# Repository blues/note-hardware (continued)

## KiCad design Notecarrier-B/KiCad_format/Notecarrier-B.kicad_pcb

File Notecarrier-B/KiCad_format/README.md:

# Notecarrier-B

This folder contains the design files for the Blues Wireless Notcarrier-B, in KiCad 7 format. They were generated by porting the original OrCad design files. For a detailed description of the porting process, see [PortingNotes](PortingNotes.md).

Components in this design are sourced from the [blues-kicad-lib](https://github.com/blues/blues-kicad-lib) library. However, with the exception of 3D models, KiCad produces self-contained project files. Thus this project can still be used without access to the library.

## Contents

- This file
 	- `README.md`
- KiCad source files
	- `Notecarrier-B.kicad_pcb`	- `Notecarrier-B.kicad_prl`	- `Notecarrier-B.kicad_pro`	- `Notecarrier-B.kicad_sch`	- `Notecarrier-B.kicad_wks`
	- `sym-lib-table`
	- `fp-info-cache`	- `fp-lib-table`
- Documentation	- `documentation/*`
- Manufacturing artefacts
	- `manufacturing/*`
- Design references
	- `reference/*`
- Validation artefacts
	- `validation/*`

## Revision History

| Revision |    Date    |   Author   | Description |
|:--------:| ---------- | ---------- | ----------- |
|     A    | 2023-03-31 | H.Raftery  | initial port from OrCAD design files, rev 14 (v2.1). |

### Original OrCad Design File Revision History

| Revision |    Date    |   Author   | Description |
|:--------:| ---------- | ---------- | ----------- |
|    12    | 25/08/2020 | G.Boschini | - Changed screw with inox version<br/>- Changed pullup resistor of EN pin to 10M |
|    14    | 25/08/2020 | M. Gregis  | - Added LiPO charger<br/>- Changed V+ to VBAT<br/>- removed BOOT signal from J21 header and replaced with GND<br/>- removed AUX5 from J22 header and replaced with VMODEM |

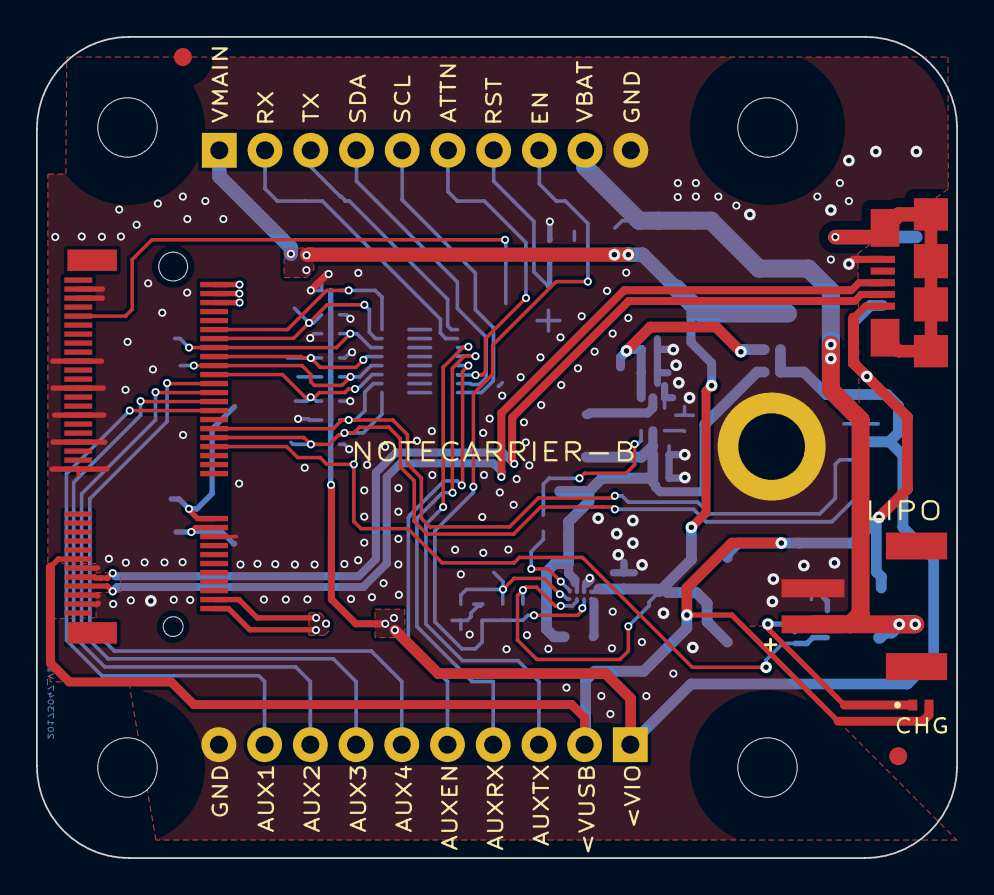
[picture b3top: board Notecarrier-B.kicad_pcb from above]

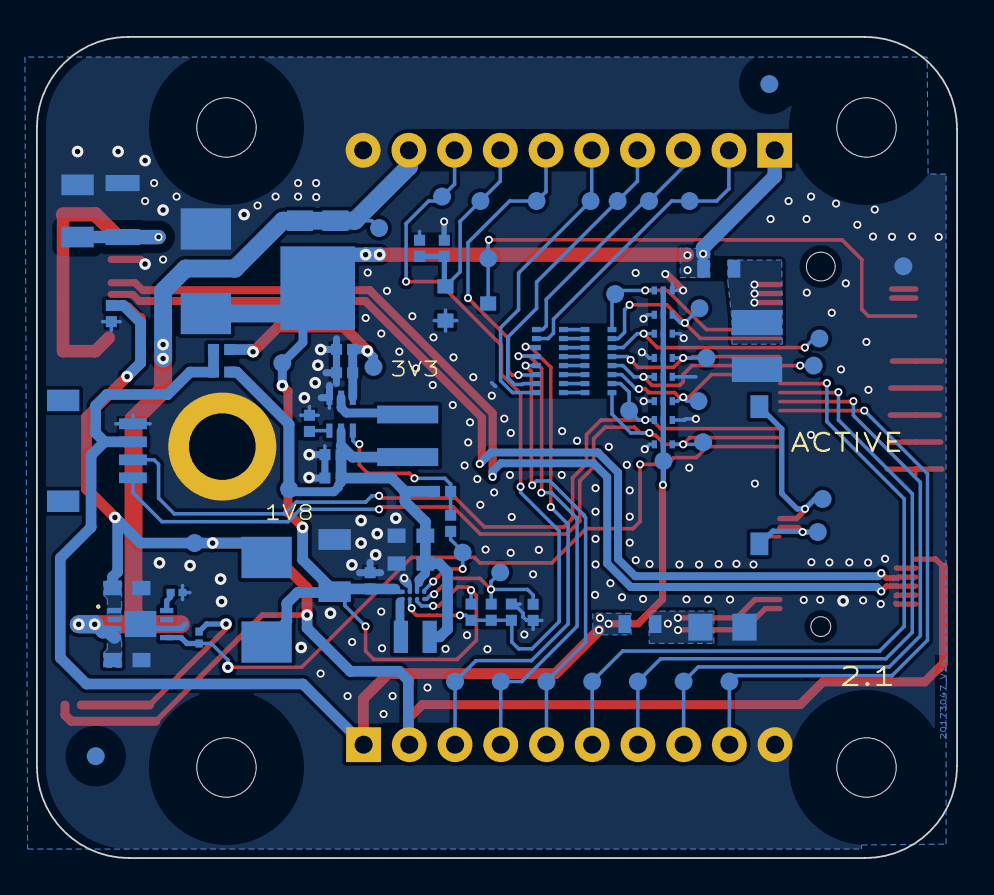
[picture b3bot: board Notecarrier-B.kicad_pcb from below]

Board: 2 copper layers, 51.1 x 45.6 mm, 96 parts (85 on the bottom side), 54 nets.

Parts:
C7, C10, C111, C115, C116: 100n/16V; CS-C-0402_NO-FILL
C8, C9: 10u/6.3V-X5R; CS-C-0402_NO-FILL
C13: 47u/16V-X5R; CS-C-1206
C14: 4.7u/6.3V-X5R; CS-C-0402_NO-FILL
C15, C16: 10u/10V-X5R; CS-C-0603
C112: 10n/1kV; CS-C-1206
C113: NU; CS-T-A
C114: NU; CS-T-B
C117, C118: 4.7u/10V/X5R; CS-C-0603
DS4, DS5, DS6, DS10: NU; SOT563
DS14: STPS3H100U; SMB
DS15: FSV1045V; TO277-3
DSW1: DIP-SW-CHS-01TB; DSS-CHS-01TB
F1: SF-0603F150-2; FS-0603
F2: 3.5A/32V; FS-0603
FID1, FID2, FID3, FID4: TPS; FIDUCIAL
H1, H2, H3, H4: MountingHole; FORO-0330-U
J19: MICROUSB-B; J-5-0065-FOS-MICROUSB10118192
J20: MDT420E01001; J-75-0050-MOS-M2-E
J21, J22: NU; J-10-0254-MDT
J23: S2B-PH-SM4-TB(LF)(SN); J-2-0200-MOS-S2B
J24: SM04B-SRSS-TBT; J-4-0100-MOS-SH
L2: 1285AS-H-2R2M=P2; LS-0806
L4: XFL4020-222MEC; LS-XFL4020
LD1: SML-P12WTT86R; LD-0402
OBJ1: 9774025151R; DIST-WASMSIM0250
Q2: AO3420; SOT23_NO-FILL
R5: 1k; RS-0201_NO-FILL
R6: 82k; RS-0402_NO-FILL
R7: 2.8k; RS-0201_NO-FILL
R10: 10M/5%; RS-0402_NO-FILL
R307: 1M; RS-1206
R318, R322, R325: 0R; RS-0402_NO-FILL
R319: 1k; RS-0402_NO-FILL
R323, R324, R326: NU; RS-0402_NO-FILL
RR1, RR2: 100R/5%; RR-8X-1506
TP1, TP2, TP3, TP4, TP5, TP6, TP7, TP8, TP10, TP11, TP12, TP13, TP14, TP15, TP17, TP18, TP20, TP21, TP22, TP23, TP24, TP25, TP26, TP28, TP29, TP30, TP31, TP32, TP33, TP34, TP38, TP39: TPS-SPEA
TVS1: SM6T6V8A; SMB
U3: MAX17225ELT; WDFN6-0200X0200
U4: TPS62748YFPT; XFBGA8
U5: MCP73831-2ACI/MC; VFDFN8-EXP
VMODEM: TPS-SPEA
VUSB: TPS-SPEA

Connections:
+1V8: C9.1, C10.1, C15.1, C16.1, L2.2, L4.2, R318.2, R326.2, TP12.1, U3.5 (IN), U4.C2 (VOS)
+3V3: C7.1, C8.1, R325.2, TP20.1, U3.1 (OUT)
/ATTN: J22.6, RR1.6 (R6.1), TP32.1
/ATTN_P: DS6.6 (K1A2), J20.54 (ATTN_P), RR2.11 (R6.2), TP18.1
/AUX1: J20.46 (AUX1), J21.9, TP1.1
/AUX2: J20.48 (AUX2), J21.8, TP2.1
/AUX3: J20.50 (AUX3), J21.7, TP3.1
/AUX4: J20.52 (AUX4), J21.6, TP7.1
/AUX5: J20.38 (NC38), R5.1, U5.5 (STAT)
/AUX_EN: J21.5, RR1.5 (R5.1), TP4.1
/AUX_EN_P: DS6.3 (K3A4), J20.56 (AUX_EN_P), RR2.12 (R5.2), TP21.1
/AUX_RX: J21.4, RR1.4 (R4.1), TP5.1
/AUX_RX_P: DS5.6 (K1A2), J20.58 (AUX_RX_P), RR2.13 (R4.2), TP22.1
/AUX_TX: J21.3, RR1.3 (R3.1), TP6.1
/AUX_TX_P: DS5.3 (K3A4), J20.60 (AUX_TX_P), RR2.14 (R3.2), TP23.1
/BOOST_EN: R324.2, TP10.1, U4.D2 (LOAD)
/EN: C116.1, J22.8, R10.1, R323.2, TP34.1, U4.B1 (EN)
/NRST: J20.67 (NRST), Q2.3 (D), TP26.1
/RST: C115.1, J22.7, Q2.1 (G), R319.2, TP33.1
/RX: J22.2, RR1.2 (R2.1), TP28.1
/RX_P: DS10.6 (K1A2), J20.62 (RX_P), RR2.15 (R2.2), TP24.1
/SCL: J22.5, RR1.8 (R8.1), TP31.1
/SCL_P: DS4.6 (K1A2), J20.40 (SCL_P), J24.4, RR2.9 (R8.2), TP15.1
/SDA: J22.4, RR1.7 (R7.1), TP30.1
/SDA_P: DS4.3 (K3A4), J20.42 (SDA_P), J24.3, RR2.10 (R7.2), TP17.1
/TX: J22.3, RR1.1 (R1.1), TP29.1
/TX_P: DS10.3 (K3A4), J20.64 (TX_P), RR2.16 (R1.2), TP25.1
/USB_DM: J19.2 (D-), J20.9 (USB_DM)
/USB_DP: J19.3 (D+), J20.7 (USB_DP)
GND: C7.2, C8.2, C9.2, C10.2, C13.2, C14.2, C15.2, C16.2, C111.2, C112.2, C113.2, C114.2, C115.2, C116.2, C117.2, C118.2, DS4.1 (A1), DS4.4 (A3), DS5.1 (A1), DS5.4 (A3), DS6.1 (A1), DS6.4 (A3), DS10.1 (A1), DS10.4 (A3), J19.5 (GND), J20.3 (GND), J20.5 (GND), J20.6 (GND), J20.11 (GND), J20.18 (GND), J20.33 (GND), J20.39 (GND), J20.45 (GND), J20.51 (GND), J20.57 (GND), J20.71 (GND), J20.73 (GND), J21.10, J22.10, J23.2, J24.1, OBJ1.1, Q2.2 (S), R6.1, R7.1, R307.2, R319.1, R322.1, TP38.1, TVS1.2 (A2), U3.3 (GND), U4.B2 (GND), U5.6 (V_{SS}), U5.9 (EP)
unnamed: C112.1, J19.6 (Shield), R307.1
unnamed: DSW1.1, J20.22 (VACT_GPS_IN)
unnamed: LD1.1 (K), R5.2
unnamed: RR1.16 (R1.2), RR2.1 (R1.1)
unnamed: RR1.15 (R2.2), RR2.2 (R2.1)
unnamed: RR1.14 (R3.2), RR2.3 (R3.1)
unnamed: RR1.13 (R4.2), RR2.4 (R4.1)
unnamed: RR1.12 (R5.2), RR2.5 (R5.1)
unnamed: RR1.11 (R6.2), RR2.6 (R6.1)
unnamed: RR1.10 (R7.2), RR2.7 (R7.1)
unnamed: RR1.9 (R8.2), RR2.8 (R8.1)
unnamed: R318.1, R324.1, U3.6 (EN)
unnamed: L4.1, U3.2 (LX)
unnamed: R6.2, U3.4 (SEL)
unnamed: R322.2, R323.1, TP8.1, U4.D1 (CTRL)
unnamed: L2.1, U4.A1 (SW)
unnamed: R7.2, U5.8 (PROG)
VACT_GPS_OUT: DSW1.2, J20.20 (VACT_GPS_OUT), TP11.1
VBAT: C117.1, DS15.1 (A1), DS15.2 (A2), J22.9, J23.1, TP39.1, U5.3 (V_{BAT}), U5.4 (V_{BAT})
VIO: DS4.2 (K2), DS4.5 (K4), DS5.2 (K2), DS5.5 (K4), DS6.2 (K2), DS6.5 (K4), DS10.2 (K2), DS10.5 (K4), F1.1, J21.1, J24.2, R325.1, R326.1, TP14.1
VIO_P: C113.1, F1.2, J20.2 (VIO_P), J20.4 (VIO_P)
VMODEM: C13.1, C14.1, DS14.1 (K), DS15.3 (C), F2.1, J22.1, R10.2, TVS1.1 (A1), U4.A2 (VIN), U4.C1 (VSEL), VMODEM.1
VMODEM_P: C114.1, F2.2, J20.70 (VMODEM_P), J20.72 (VMODEM_P), J20.74 (VMODEM_P)
VUSB: C111.1, C118.1, DS14.2 (A), J19.1 (VBUS), J20.13 (VUSB), J21.2, LD1.2 (A), U5.1 (V_{DD}), U5.2 (V_{DD}), VUSB.1

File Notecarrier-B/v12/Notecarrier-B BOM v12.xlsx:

PROJECT |  | 2017-3047 (NOTECARRIER-M2-B) |  | Blues Inc
REVISION |  | 12
SCHEMATIC |  | 20173047_NOTECARRIER-M2-B_V12
DATA |  | 25/08/2020
Item | Quantity | Reference | Part | MPN | Description | Temperature | Type | Package
1 | 1 | CS1 | CS V11 2L 35um |  | C.S. NOTECARRIER-M2-B V11 (45.62X45.62)mm 2L/SO/SR ENIG TG150 sp=1.6mm Cu=35um | TG150
2 | 5 | C7,C10,C111,C115,C116 | 100n/16V |  | CHIP CERAMIC CAPACITOR 100nF 16V 10% X7R 0402 |  | SMD | CS-C-0402
3 | 2 | C8,C9 | 10u/6.3V-X5R |  | CHIP CERAMIC CAPACITOR 10uF 6.3V 20% X5R 0402 | -55°..+85° | SMD | CS-C-0402
4 | 1 | C13 | 47u/16V-X5R |  | CHIP CERAMIC CAPACITOR 47uF 16V 20% X5R 1206 |  | SMD | CS-C-1206
5 | 1 | C14 | 4.7u/6.3V-X5R |  | CHIP CERAMIC CAPACITOR 4.7uF 6.3V 20% X5R 0402 |  | SMD | CS-C-0402
6 | 2 | C15,C16 | 10u/10V-X5R |  | CHIP CERAMIC CAPACITOR 10uF 10V 10% X5R 0603 |  | SMD | CS-C-0603
7 | 1 | C112 | 10n/1kV |  | CHIP CERAMIC CAPACITOR 10nF 1000V 10% X7R 1206 |  | SMD | CS-C-1206
8 | 1 | DS14 | STPS3H100U | STPS3H100U | DIODE SCHOTTKY 3A 100V STPS3H100U SMB SMT |  | SMD | SMB
9 | 1 | DS15 | FSV1045V | FSV1045V | DIODE SCHOTTKY 10A 45V FSV1045V TO277-3 SMT | -55°..+150° | SMD | TO277-3
10 | 1 | F1 | SF-0603F150-2 | SF-0603F150-2 | FAST BLOW FUSE 1.5A 32V 0603 SF-0603F150-2 BOURNS SMT | -40°..+105° | SMD | FS-0603
11 | 1 | F2 | 3.5A/32V | 0603SFV350F/32-2 | FAST BLOW FUSE 3.5A 32V 0603 0603SFV350F/32-2 LITTELFUSE SMT | -55°..+125° | SMD | FS-0603
12 | 1 | J19 | MICROUSB-B | 10118192-0001LF | CONNECTOR USB F/90° TIPO MICRO-B C.S. 10118192-0001LF FCI SMT | -30°..+85° | SMD | J-5-0065-FOS-MICROUSB10118192
13 | 1 | J20 | MDT420E01001 |  | CONNECTOR M.2 75P M/90° P=0.5 MDT420E01001 AMPHENOL SMT | -40°..+80° | SMD | J-75-0050-MOS-M2-E
14 | 1 | J21 | HEADER STRIP 9 PIN |  | HEADER STRIP 1P M/D P=2.54 CH3140V100 |  | THT | J-10-0254-MDT
15 | 1 | J22 | HEADER STRIP 9 PIN |  | HEADER STRIP 1P M/D P=2.54 CH3140V100 |  | THT | J-9-0254-MDT
16 | 1 | L2 | 1285AS-H-2R2M=P2 | 1285AS-H-2R2M=P2 | INDUCTOR 2.2uH 1.5A 20% 0806 1285AS-H-2R2M=P2 MURATA SMT | -40°..+85° | SMD | LS-0806
17 | 1 | L4 | XFL4020-222MEC | XFL4020-222MEC | INDUCTOR 2.2 uH 3.1A 20% XFL4020-222MEC COILCRAFT SMT | -40°..+125° | SMD | LS-XFL4020
18 | 1 | OBJ1 | 9774025151R |  | ROUND STANDOFF STEEL 5.1X2.5 9774025151R W.E SMT |  | SMD | DIST-WASMSIM0250
19 | 1 | Q2 | AO3420 |  | TRANSISTOR MOSFET N AO3420 SOT-23 ALPHA-OMEGA SMT | -55°..+150° | SMD | SOT23
20 | 2 | RR1,RR2 | 100R/5% |  | RESISTOR NETWORK 8R sing. 100R 5% 1506 CAY16-101J8LF BOURNS SMT | -55°..+125° | SMD | RR-8X-1506
21 | 1 | R6 | 82k |  | CHIP RESISTOR 82K 0402 1/16W 1% | -55°..+155° | SMD | RS-0402
22 | 1 | R10 | 10M/5% |  | CHIP RESISTOR 10M 0402 1/8W 5% | -55°..+125° | SMD | RS-0402
23 | 1 | R307 | 1M |  | CHIP RESISTOR 1M 1206 1/4W 1% |  | SMD | RS-1206
24 | 1 | R317 | 0R/5%/AS |  | CHIP RESISTOR 0R 0805 1/8W 5% ANTI-SULFUR | -55°..+155° | SMD | RS-0805
25 | 2 | R318,R322 | 0R |  | CHIP RESISTOR 0R 0402 1/16W 1% |  | SMD | RS-0402
26 | 1 | R319 | 1k |  | CHIP RESISTOR 1K 0402 1/16W 1% | -55°..+155° | SMD | RS-0402
27 | 1 | SW1 | CJS-1200TA |  | SWITCH SLIDE SPDT ON-ON. CJS-1200TA NIDEC COPAL ELECTRONICS SMT | -40°..+85° | SMD | SW-CJS1200TA
28 | 1 | TVS1 | SM6T6V8A |  | DIODE TVS TRANSIL UNIDIR. 600W 6.8V SM6T6V8A SMB SMT |  | SMD | SMB
29 | 1 | U3 | MAX17225ELT | MAX17225ELT+T | IC MAX17225ELT+T MAXIM W-DFN6 SMT | -40°..+85° | SMD | WDFN6-0200X0200
30 | 1 | U4 | TPS62748YFPT | TPS62748YFPT | IC TPS62748YFPT TEXAS DSBGA8 SMT | -40°..+85° | SMD | XFBGA8
 | 38
MECHANICAL
1 | 1 | ASS1 | SCREW M2.5x4 |  | DIN 912 M2.5x4 HEX SOCKET HEAD CAP SCREW, FULLY-THREADED SHAFT, A2 STAINLESS |  | THT
 | 1
NOT MOUNTED
1 | 1 | C113 | NU | F930J107KAA | CHIP CAP.TANT. 100uF 6.3V 10% CASE A F930J107KAA AVX | -55°..+125° | SMD | CS-T-A
2 | 1 | C114 | NU | F930J227KBA | CHIP CAP.TANT. 220uF 6.3V 10% CASE B F930J227KBA AVX | -55°..+125° | SMD | CS-T-B
3 | 4 | DS4,DS5,DS6,DS10 | NU | BAV99BRVA-7 | DIODE ARRAY 0.2A 75V BAV99BRVA-7 SOT563 DIODES SMT | -65°..+150° | SMD | SOT563
4 | 4 | FID1,FID2,FID3,FID4 | TPS |  | FIDUCIAL |  | SMD | FIDUCIAL
5 | 2 | R323,R324 | NU |  | CHIP RESISTOR 0402 |  | SMD | RS-0402

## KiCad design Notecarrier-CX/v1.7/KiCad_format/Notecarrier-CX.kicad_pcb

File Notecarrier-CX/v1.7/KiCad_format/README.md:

# Notecarrier-CX v1.7 — KiCad format

This directory contains the design files for the Blues **Notecarrier-CX**
v1.7 in **KiCad 9** format. They were generated by porting the original
Altium Designer design files (project `100544_notecarrier-cx`) and validated
against the shipped BOM, the production gerbers, and the shipped ODB++
netlist — see
[`documentation/Porting-Notes.md`](documentation/Porting-Notes.md) and
[`validation/`](validation/).

## Contents

| Path | Description |
|---|---|
| `Notecarrier-CX.kicad_pro` / `Notecarrier-CX.kicad_prl` | KiCad project |
| `Notecarrier-CX.kicad_sch` | Root schematic |
| `Notecarrier-CX_IO-Connection.kicad_sch`, `Notecarrier-CX_Notecard-Connection.kicad_sch`, `Notecarrier-CX_Power.kicad_sch`, `Notecarrier-CX_MCU.kicad_sch` | Child sheets (the Altium cover and block-diagram sheets are not ported) |
| `Notecarrier-CX.kicad_pcb` | 4-layer board (castellated edges; zone fills preserved from the Altium import — do not refill) |
| `Notecarrier-CX.kicad_wks` | Drawing sheet (shared Blues template) |
| `Notecarrier-CX-altium-import.kicad_sym` / `Notecarrier-CX-altium-import.pretty/` | Project symbol/footprint libraries captured during the import |
| `sym-lib-table` / `fp-lib-table` | Library tables (the original Altium lib nicknames are aliased to the project library) |
| `documentation/` | Porting notes and plotted schematic/board PDFs |
| `manufacturing/Notecarrier-CX_RevA.zip` | Gerbers + Excellon drills exported from KiCad (authoritative production package: [`../FAB/`](../FAB/) ) |
| `validation/` | ERC/DRC reports, per-layer gerber diffs, BOM comparison, ODB++ netlist cross-check, KiCanvas screenshots |

The project is self-contained. Note: R4 (0R) is not populated in the
production build and is flagged DNP; the castellated header positions
P1/P2/P4 are bare-board features and are excluded from the BOM, matching
the shipped production BOM.

## Revision History

| Revision | Date | Author | Notes |
|---|---|---|---|
| A | 2026-07-28 | Blues Inc | Initial port of Notecarrier-CX v1.7 from Altium Designer sources, KiCad 9.0.9 |

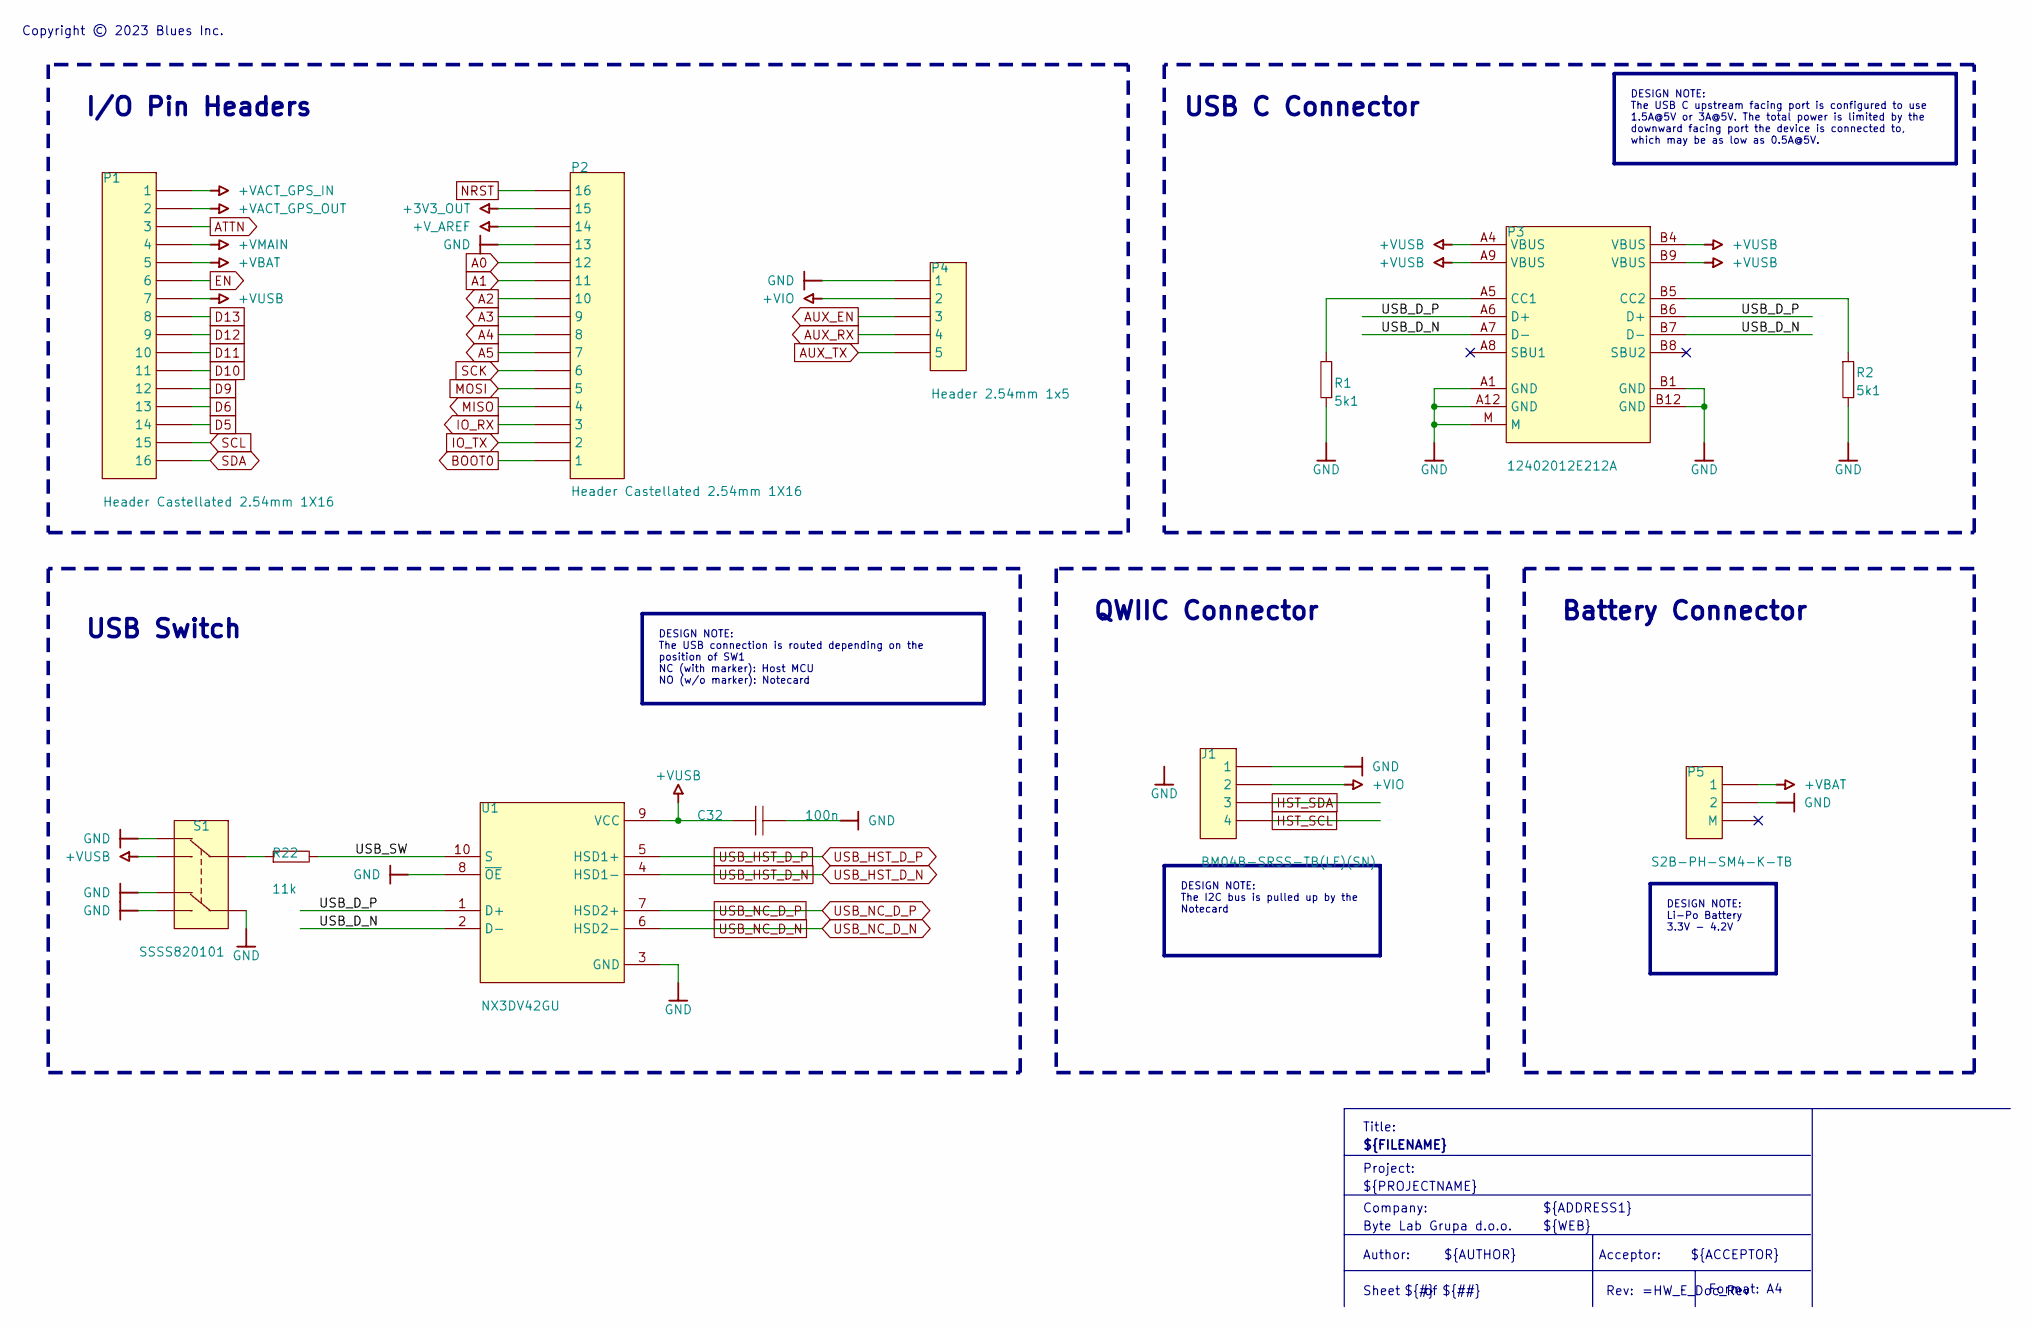
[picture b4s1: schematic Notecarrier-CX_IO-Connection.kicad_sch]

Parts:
C32: 100n; C-0402; MANUFACTURER PART NUMBER N/A
J1: BM04B-SRSS-TB(LF)(SN); Conn BM04B-SRSS-TB(LF)(SN); MANUFACTURER PART NUMBER BM04B-SRSS-TB(LF)(SN)
P1, P2: Header Castellated 2.54mm 1X16; Castellated Header 2.54mm 1X16; MANUFACTURER PART NUMBER N/A
P3: 12402012E212A; CONN_12402012E212A; MANUFACTURER PART NUMBER 12402012E212A
P4: Header 2.54mm 1x5; Castellated Header 2.54mm 1X5; MANUFACTURER PART NUMBER DS1021-1*5SF1-1
P5: S2B-PH-SM4-K-TB; Conn S2B-PH-SM4; MANUFACTURER PART NUMBER S2B-PH-SM4-K-TB(LF)(SN)
R1, R2: 5k1; R-0402; MANUFACTURER PART NUMBER N/A
R22: 11k; R-0402; MANUFACTURER PART NUMBER N/A
S1: SSSS820101; Slide Switch SSSS820101; MANUFACTURER PART NUMBER SSSS820101
U1: NX3DV42GU; QFN40P140X180X50-10N; MANUFACTURER PART NUMBER NX3DV42GU

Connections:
+3V3_OUT: P2.15; also elsewhere on the board
+VACT_GPS_IN: P1.1; also elsewhere on the board
+VACT_GPS_OUT: P1.2; also elsewhere on the board
+VBAT: P1.5, P5.1; also elsewhere on the board
+VIO: J1.2, P4.2; also elsewhere on the board
+VMAIN: P1.4; also elsewhere on the board
+VUSB: C32.2, P1.7, P3.A4 (VBUS), P3.A9 (VBUS), P3.B4 (VBUS), P3.B9 (VBUS), S1.1, U1.9 (VCC); also elsewhere on the board
+V_AREF: P2.14; also elsewhere on the board
/IO Connection/USB_D_N: P3.A7 (D-), P3.B7 (D-), U1.2 (D-)
/IO Connection/USB_D_P: P3.A6 (D+), P3.B6 (D+), U1.1 (D+)
/IO Connection/USB_SW: R22.2, U1.10 (S)
A0: P2.12; also elsewhere on the board
A1: P2.11; also elsewhere on the board
A2: P2.10; also elsewhere on the board
A3: P2.9; also elsewhere on the board
A4: P2.8; also elsewhere on the board
A5: P2.7; also elsewhere on the board
ATTN: P1.3; also elsewhere on the board
AUX_EN: P4.3; also elsewhere on the board
AUX_RX: P4.4; also elsewhere on the board
AUX_TX: P4.5; also elsewhere on the board
BOOT0: P2.1; also elsewhere on the board
D5: P1.14; also elsewhere on the board
D6: P1.13; also elsewhere on the board
D9: P1.12; also elsewhere on the board
D10: P1.11; also elsewhere on the board
D11: P1.10; also elsewhere on the board
D12: P1.9; also elsewhere on the board
D13: P1.8; also elsewhere on the board
EN: P1.6; also elsewhere on the board
GND: C32.1, J1.1, J1.M, P2.13, P3.A1 (GND), P3.A12 (GND), P3.B1 (GND), P3.B12 (GND), P3.M, P4.1, P5.2, R1.1, R2.2, S1.3, S1.4, S1.5, S1.6, U1.3 (GND), U1.8 (~OE); also elsewhere on the board
HST_SCL: J1.4, P1.15; also elsewhere on the board
HST_SDA: J1.3, P1.16; also elsewhere on the board
IO_RX: P2.3; also elsewhere on the board
IO_TX: P2.2; also elsewhere on the board
MISO: P2.4; also elsewhere on the board
MOSI: P2.5; also elsewhere on the board
NRST: P2.16; also elsewhere on the board
unnamed: P3.A5 (CC1), R1.2
unnamed: P3.B5 (CC2), R2.1
unnamed: R22.1, S1.2
SCK: P2.6; also elsewhere on the board
USB_HST_D_N: U1.4 (HSD1-); also elsewhere on the board
USB_HST_D_P: U1.5 (HSD1+); also elsewhere on the board
USB_NC_D_N: U1.6 (HSD2-); also elsewhere on the board
USB_NC_D_P: U1.7 (HSD2+); also elsewhere on the board

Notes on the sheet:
Copyright © 2023 Blues Inc.
${REVISION}
Sheet
${#}
${COMPANY}
Company:
${AUTHOR}
Battery Connector
${FILENAME}
${ACCEPTOR}
Acceptor:
Title:
Author:
${ADDRESS1}
Project:
Rev:
${WEB}
USB C Connector
QWIIC Connector
${PROJECTNAME}
I/O Pin Headers
Format: A4
USB Switch
${##}
DESIGN NOTE: The I2C bus is pulled up by the Notecard
DESIGN NOTE: Li-Po Battery 3.3V - 4.2V
DESIGN NOTE: The USB C upstream facing port is configured to use 1.5A@5V or 3A@5V. The total power is limited by the downward facing port the device is connected to, which may be as low as 0.5A@5V.
DESIGN NOTE: The USB connection is routed depending on the position of SW1 NC (with marker): Host MCU NO (w/o marker): Notecard

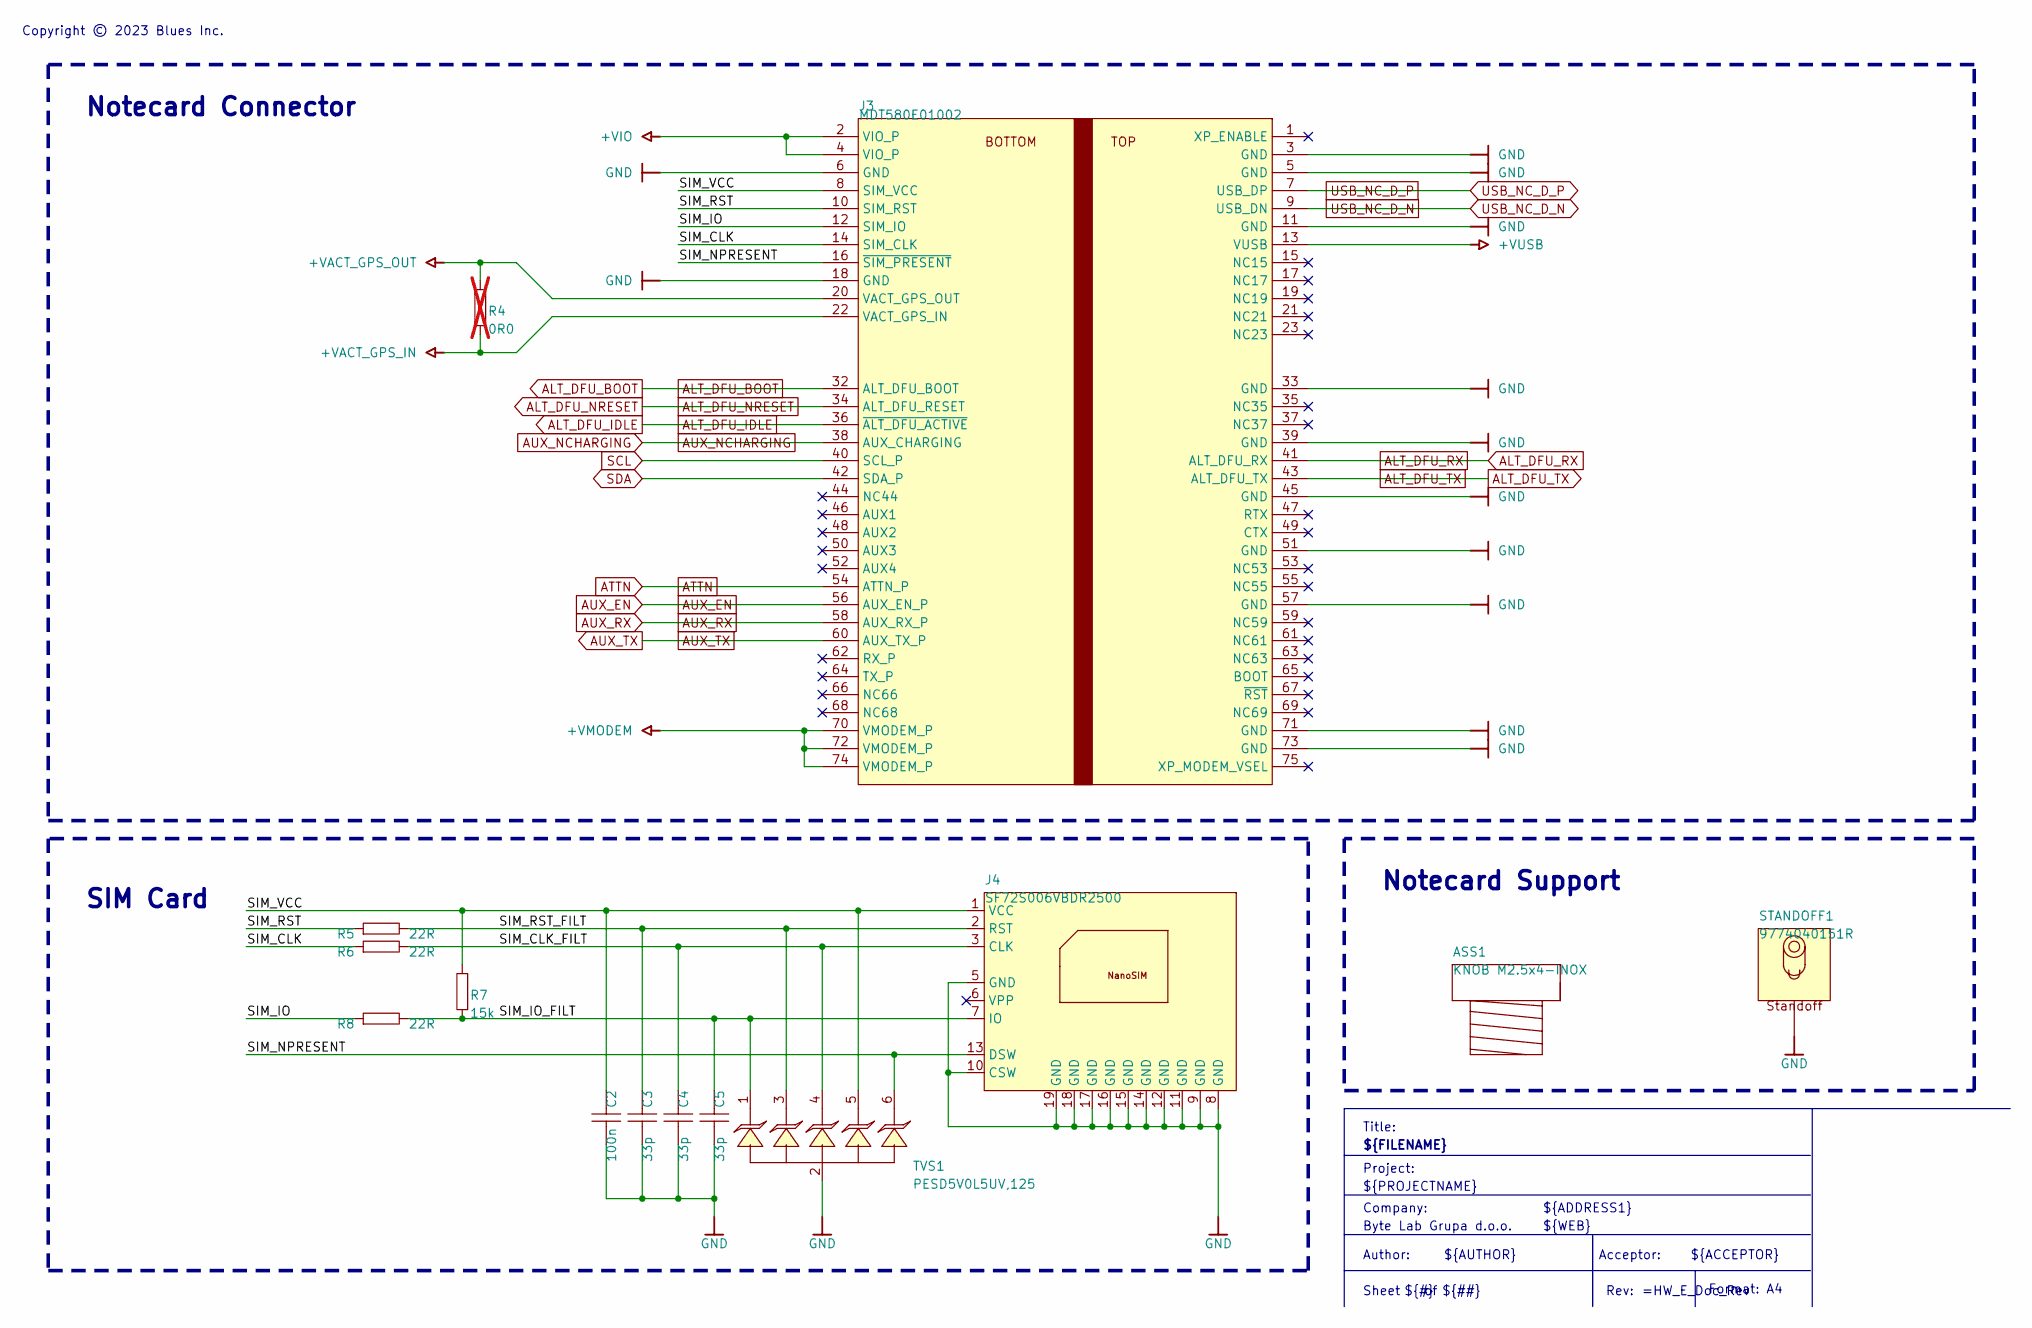
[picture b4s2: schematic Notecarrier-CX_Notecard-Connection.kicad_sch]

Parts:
ASS1: KNOB M2.5x4-INOX; MANUFACTURER PART NUMBER M2.5X4/D7985-A2
C2: 100n; C-0402; MANUFACTURER PART NUMBER N/A
C3, C4, C5: 33p; C-0402; MANUFACTURER PART NUMBER N/A
J3: MDT580E01002; CONN_MDT580E01002; MANUFACTURER PART NUMBER MDT580E01002
J4: SF72S006VBDR2500; J-NANOSIM-SF72S006VBA; MANUFACTURER PART NUMBER SF72S006VBDR2500
R4: 0R0; R-0603; MANUFACTURER PART NUMBER N/A; not fitted
R5, R6, R8: 22R; R-0402; MANUFACTURER PART NUMBER N/A
R7: 15k; R-0402; MANUFACTURER PART NUMBER N/A
STANDOFF1: 9774040151R; STANDOFF_9774040151R; MANUFACTURER PART NUMBER 9774040151R
TVS1: PESD5V0L5UV,125; SOT666; MANUFACTURER PART NUMBER PESD5V0L5UV,125

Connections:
+VACT_GPS_IN: J3.22 (VACT_GPS_IN), R4.1; also elsewhere on the board
+VACT_GPS_OUT: J3.20 (VACT_GPS_OUT), R4.2; also elsewhere on the board
+VIO: J3.2 (VIO_P), J3.4 (VIO_P); also elsewhere on the board
+VMODEM: J3.70 (VMODEM_P), J3.72 (VMODEM_P), J3.74 (VMODEM_P); also elsewhere on the board
+VUSB: J3.13 (VUSB); also elsewhere on the board
/Notecard Connection/SIM_CLK: J3.14 (SIM_CLK), R6.1
/Notecard Connection/SIM_CLK_FILT: C4.2, J4.3 (CLK), R6.2, TVS1.4 (C4)
/Notecard Connection/SIM_IO: J3.12 (SIM_IO), R8.1
/Notecard Connection/SIM_IO_FILT: C5.2, J4.7 (IO), R7.1, R8.2, TVS1.1 (C1)
/Notecard Connection/SIM_NPRESENT: J3.16 (~SIM_PRESENT), J4.13 (DSW), TVS1.6 (C6)
/Notecard Connection/SIM_RST: J3.10 (SIM_RST), R5.1
/Notecard Connection/SIM_RST_FILT: C3.2, J4.2 (RST), R5.2, TVS1.3 (C3)
/Notecard Connection/SIM_VCC: C2.2, J3.8 (SIM_VCC), J4.1 (VCC), R7.2, TVS1.5 (A5)
ALT_DFU_BOOT: J3.32 (ALT_DFU_BOOT); also elsewhere on the board
ALT_DFU_IDLE: J3.36 (~ALT_DFU_ACTIVE); also elsewhere on the board
ALT_DFU_NRESET: J3.34 (ALT_DFU_RESET); also elsewhere on the board
ALT_DFU_RX: J3.41 (ALT_DFU_RX); also elsewhere on the board
ALT_DFU_TX: J3.43 (ALT_DFU_TX); also elsewhere on the board
ATTN: J3.54 (ATTN_P); also elsewhere on the board
AUX_EN: J3.56 (AUX_EN_P); also elsewhere on the board
AUX_NCHARGING: J3.38 (AUX_CHARGING); also elsewhere on the board
AUX_RX: J3.58 (AUX_RX_P); also elsewhere on the board
AUX_TX: J3.60 (AUX_TX_P); also elsewhere on the board
GND: C2.1, C3.1, C4.1, C5.1, J3.3 (GND), J3.5 (GND), J3.6 (GND), J3.11 (GND), J3.18 (GND), J3.33 (GND), J3.39 (GND), J3.45 (GND), J3.51 (GND), J3.57 (GND), J3.71 (GND), J3.73 (GND), J4.5 (GND), J4.8 (GND), J4.9 (GND), J4.10 (CSW), J4.11 (GND), J4.12 (GND), J4.14 (GND), J4.15 (GND), J4.16 (GND), J4.17 (GND), J4.18 (GND), J4.19 (GND), STANDOFF1.MH1, TVS1.2 (A2); also elsewhere on the board
HST_SCL: J3.40 (SCL_P); also elsewhere on the board
HST_SDA: J3.42 (SDA_P); also elsewhere on the board
USB_NC_D_N: J3.9 (USB_DN); also elsewhere on the board
USB_NC_D_P: J3.7 (USB_DP); also elsewhere on the board

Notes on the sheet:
Title:
Notecard Connector
${AUTHOR}
${WEB}
Notecard Support
Company:
Copyright © 2023 Blues Inc.
${FILENAME}
Format: A4
Acceptor:
Rev:
${#}
SIM Card
${PROJECTNAME}
Author:
${REVISION}
${COMPANY}
Sheet
${ADDRESS1}
${ACCEPTOR}
Project:
${##}

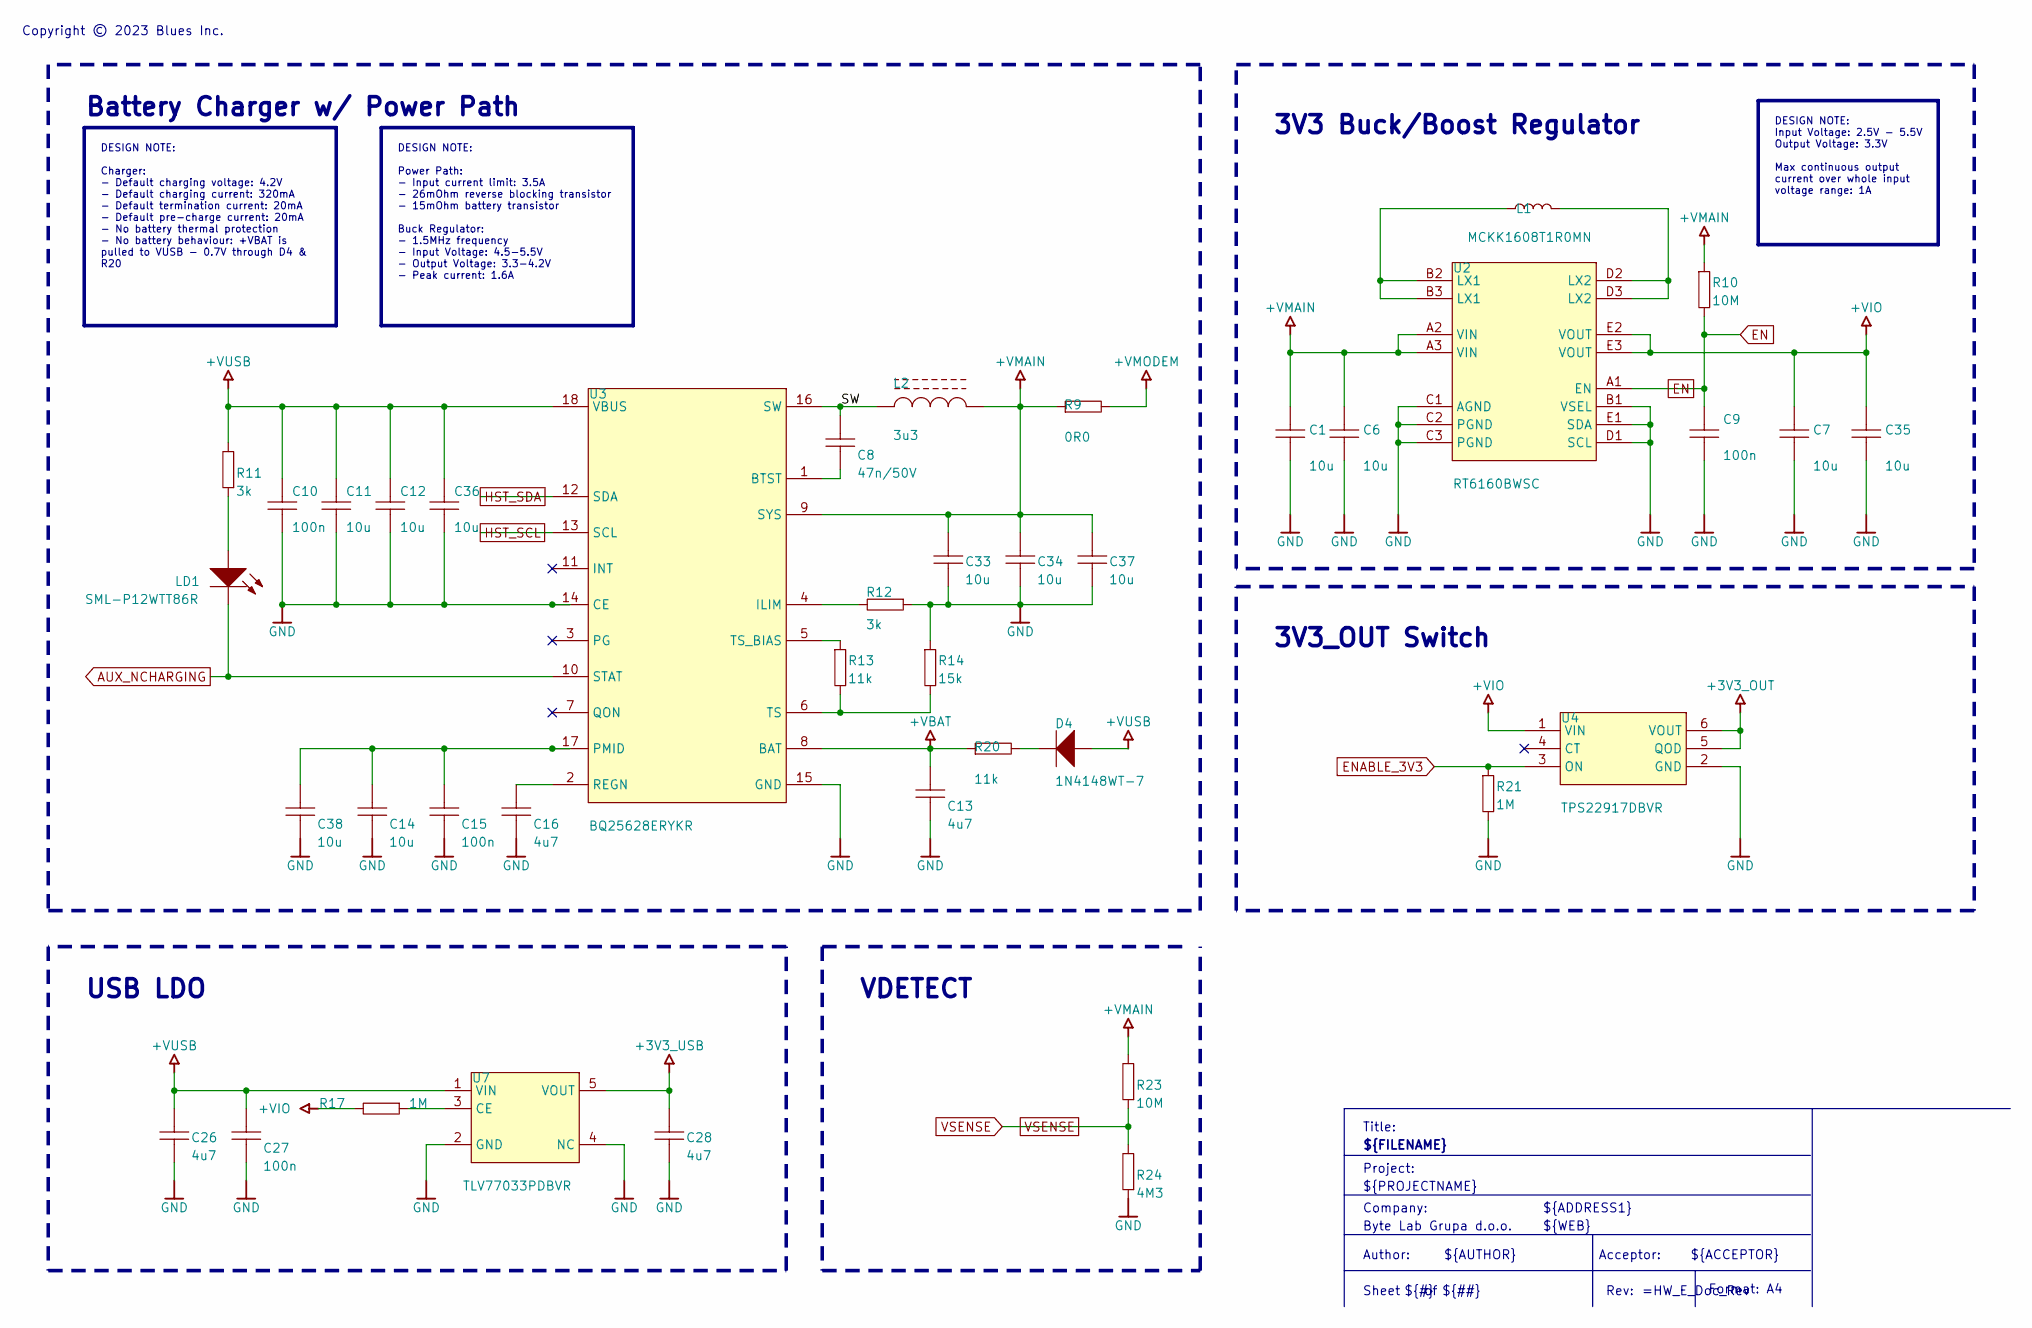
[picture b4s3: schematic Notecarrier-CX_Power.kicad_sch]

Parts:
C1, C6, C7, C11, C12, C14, C33, C34, C35, C36, C37, C38: 10u; C-0603; MANUFACTURER PART NUMBER N/A
C8: 47n/50V; C-0402; MANUFACTURER PART NUMBER N/A
C9, C10, C15, C27: 100n; C-0402; MANUFACTURER PART NUMBER N/A
C13, C16, C26, C28: 4u7; C-0603; MANUFACTURER PART NUMBER N/A
D4: 1N4148WT-7; SOD-523F; MANUFACTURER PART NUMBER 1N4148WT-7
L1: MCKK1608T1R0MN; L-0603; MANUFACTURER PART NUMBER MCKK1608T1R0MN
L2: 3u3; L-1008; MANUFACTURER PART NUMBER MAMK2520T3R3M
LD1: SML-P12WTT86R; LED-0402; MANUFACTURER PART NUMBER SML-P12WTT86R
R9: 0R0; R-0603; MANUFACTURER PART NUMBER N/A
R10, R23: 10M; R-0402; MANUFACTURER PART NUMBER N/A
R11, R12: 3k; R-0402; MANUFACTURER PART NUMBER N/A
R13, R20: 11k; R-0402; MANUFACTURER PART NUMBER N/A
R14: 15k; R-0402; MANUFACTURER PART NUMBER N/A
R17, R21: 1M; R-0402; MANUFACTURER PART NUMBER N/A
R24: 4M3; R-0402; MANUFACTURER PART NUMBER N/A
U2: RT6160BWSC; BGA15N40P3X5_230x140x60; MANUFACTURER PART NUMBER RT6160BWSC
U3: BQ25628ERYKR; QFN40P300X250X80-18N; MANUFACTURER PART NUMBER BQ25628ERYKR
U4: TPS22917DBVR; SOT-23-6 Thin; MANUFACTURER PART NUMBER TPS22917DBVR
U7: TLV77033PDBVR; SOT-23-5(M5); MANUFACTURER PART NUMBER TLV77033PDBVR

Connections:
+3V3_OUT: U4.5 (QOD), U4.6 (VOUT); also elsewhere on the board
+3V3_USB: C28.1, U7.5 (VOUT); also elsewhere on the board
+VBAT: C13.2, R20.1, U3.8 (BAT); also elsewhere on the board
+VIO: C7.2, C35.2, R17.2, U2.E2 (VOUT), U2.E3 (VOUT), U4.1 (VIN); also elsewhere on the board
+VMAIN: C1.2, C6.2, C33.1, C34.1, C37.1, L2.2, R9.1, R10.1, R23.2, U2.A2 (VIN), U2.A3 (VIN), U3.9 (SYS); also elsewhere on the board
+VMODEM: R9.2; also elsewhere on the board
+VUSB: C10.1, C11.1, C12.1, C26.1, C27.2, C36.1, D4.1 (A), R11.2, U3.18 (VBUS), U7.1 (VIN); also elsewhere on the board
/Power/SW: C8.2, L2.1, U3.16 (SW)
AUX_NCHARGING: LD1.2 (K), U3.10 (STAT); also elsewhere on the board
EN: C9.1, R10.2, U2.A1 (EN); also elsewhere on the board
ENABLE_3V3: R21.1, U4.3 (ON); also elsewhere on the board
GND: C1.1, C6.1, C7.1, C9.2, C10.2, C11.2, C12.2, C13.1, C14.1, C15.1, C16.1, C26.2, C27.1, C28.2, C33.2, C34.2, C35.1, C36.2, C37.2, C38.1, R12.1, R14.1, R21.2, R24.1, U2.B1 (VSEL), U2.C1 (AGND), U2.C2 (PGND), U2.C3 (PGND), U2.D1 (SCL), U2.E1 (SDA), U3.14 (CE), U3.15 (GND), U4.2 (GND), U7.2 (GND), U7.4 (NC); also elsewhere on the board
HST_SCL: U3.13 (SCL); also elsewhere on the board
HST_SDA: U3.12 (SDA); also elsewhere on the board
unnamed: D4.2 (K), R20.2
unnamed: L1.1, U2.B2 (LX1), U2.B3 (LX1)
unnamed: L1.2, U2.D2 (LX2), U2.D3 (LX2)
unnamed: LD1.1 (A), R11.1
unnamed: C8.1, U3.1 (BTST)
unnamed: R12.2, U3.4 (ILIM)
unnamed: C14.2, C15.2, C38.2, U3.17 (PMID)
unnamed: C16.2, U3.2 (REGN)
unnamed: R13.2, R14.2, U3.6 (TS)
unnamed: R13.1, U3.5 (TS_BIAS)
unnamed: R17.1, U7.3 (CE)
VSENSE: R23.1, R24.2; also elsewhere on the board

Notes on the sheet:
${ACCEPTOR}
${REVISION}
Copyright © 2023 Blues Inc.
${COMPANY}
Project:
3V3 Buck/Boost Regulator
Author:
3V3_OUT Switch
${PROJECTNAME}
VDETECT
Battery Charger w/ Power Path
Format: A4
${AUTHOR}
Rev:
${FILENAME}
Acceptor:
Title:
${ADDRESS1}
${##}
${#}
USB LDO
Sheet
${WEB}
Company:
DESIGN NOTE: Power Path: - Input current limit: 3.5A - 26mOhm reverse blocking transistor - 15mOhm battery transistor Buck Regulator: - 1.5MHz frequency - Input Voltage: 4.5-5.5V - Output Voltage: 3.3-4.2V - Peak current: 1.6A
DESIGN NOTE: Charger: - Default charging voltage: 4.2V - Default charging current: 320mA - Default termination current: 20mA - Default pre-charge current: 20mA - No battery thermal protection - No battery behaviour: +VBAT is pulled to VUSB - 0.7V through D4 & R20
DESIGN NOTE: Input Voltage: 2.5V - 5.5V Output Voltage: 3.3V Max continuous output current over whole input voltage range: 1A
